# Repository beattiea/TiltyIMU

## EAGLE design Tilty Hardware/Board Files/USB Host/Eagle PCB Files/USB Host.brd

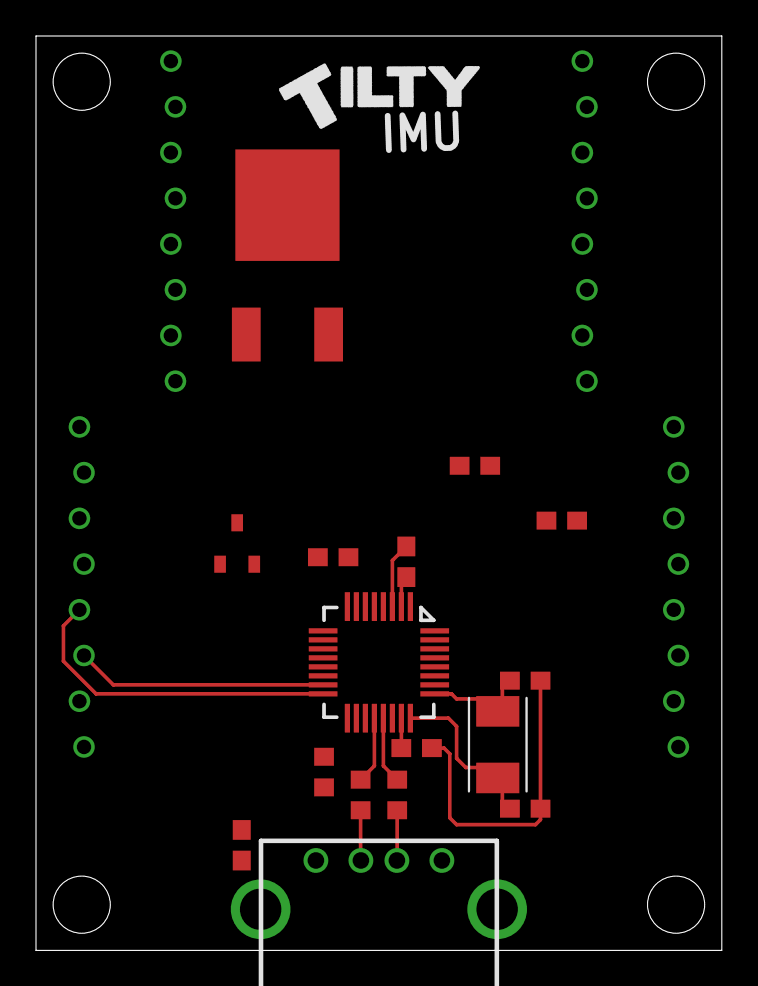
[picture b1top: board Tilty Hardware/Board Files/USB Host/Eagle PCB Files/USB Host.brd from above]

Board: 2 copper layers, 38.1 x 50.8 mm, 20 parts (0 on the bottom side), 16 nets.

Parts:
C1, C2, C7: 0.1uF; C0603
C3, C4: 22pF; C0603
C5, C8: 4.7uF; C0603
C6: 1uF; C0603
JP1, JP2, JP3, JP4: 8-PIN_HEADER; 8-PIN_RECEPTACLE_LOCK_NO-SS
R1, R2: 33; R0603
R3: 4.7K; R0603
U1: MAX3421E; TQFP32_8MIL
U2: AP7313SOT23R; SOT23
U3: LM2931; TO263
U$1: USB_SOCKETTYPE-A; USB_SOCKET
X1: CRYSTAL-TXC-7A

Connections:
+3V3: C1.1, C2.1, C6.1, JP1.P$1, R3.2, U1.2, U1.23, U2.P$2
+5V: C5.1, C8.1, JP4.P$1, U2.P$3, U3.P$3, U$1.P$1
GND: C1.2, C2.2, C3.1, C4.1, C5.2, JP2.P$8, JP3.P$8, JP4.P$2, U1.3, U1.19, U$1.P$4, U$1.P$5, U$1.P$6
INT: R3.1, U1.18
MISO: JP2.P$6, U1.15
MOSI: JP2.P$5, U1.16
unnamed: R2.2, U1.20
unnamed: R1.2, U1.21
unnamed: R2.1, U$1.P$2
unnamed: R1.1, U$1.P$3
unnamed: C4.2, U1.24, X1.P$1
unnamed: C3.2, U1.25, X1.P$2
unnamed: C6.2, U2.P$1
unnamed: C7.2, C8.2, U3.P$1
SCK: JP3.P$5, U1.13
VCC: C7.1, JP2.P$7, U3.P$2

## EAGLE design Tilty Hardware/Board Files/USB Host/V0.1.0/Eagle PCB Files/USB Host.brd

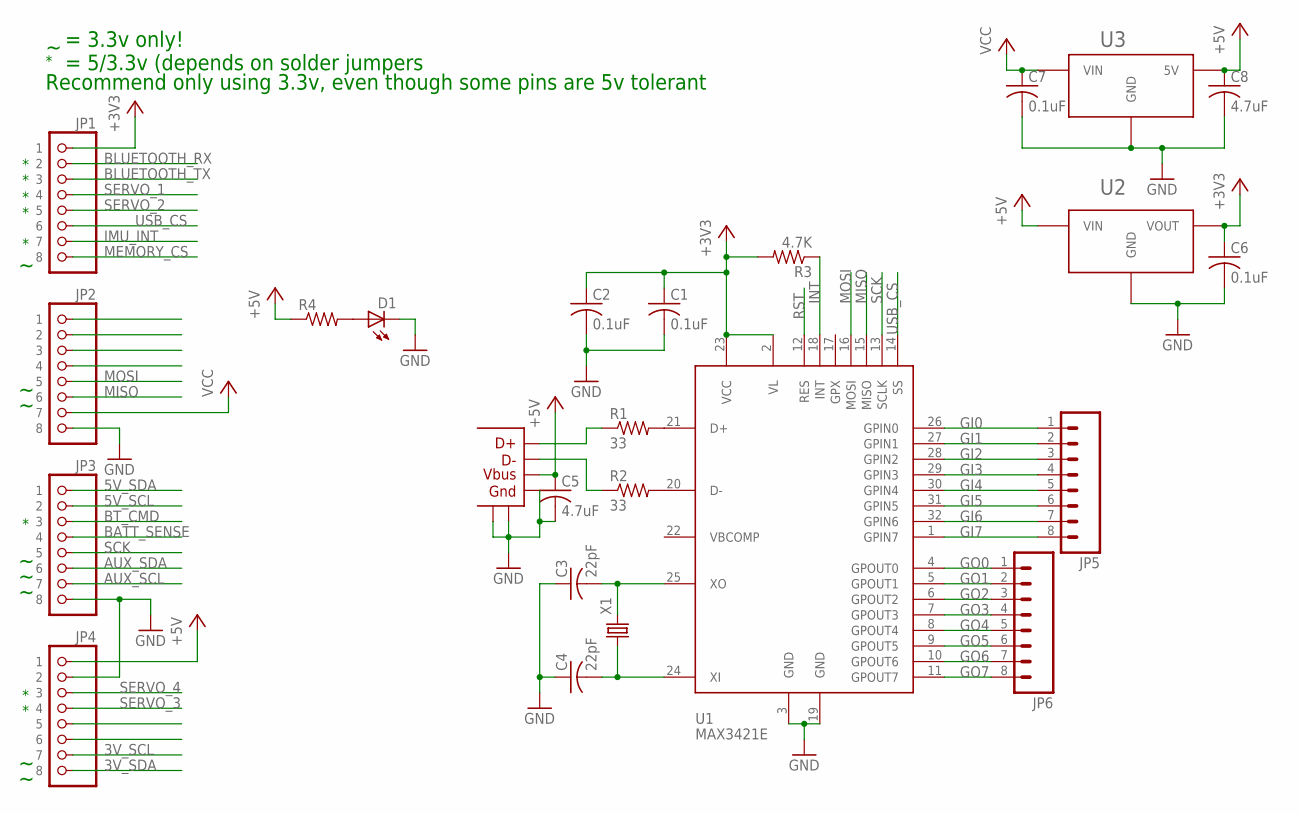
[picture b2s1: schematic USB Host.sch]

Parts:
C1, C2, C6, C7: 0.1uF; C0603
C3, C4: 22pF; C0603
C5, C8: 4.7uF; C0603
D1: LED-GREENLED-0805_NO_SILK; LED-0805
JP1, JP2, JP3, JP4: 8-PIN_HEADER; 8-PIN_RECEPTACLE_LOCK_NO-SS
JP5, JP6: M081X08; 1X08
R1, R2: 33; R0603
R3: 4.7K; R0603
R4: R-US_R0603; R0603
U1: MAX3421E; TQFP32_8MIL
U2: AP7313SOT23R; SOT23
U3: LM2931; TO263
U$1: USB_SOCKETTYPE-A; USB_SOCKET; PART# USB-A1HSW6
X1: CRYSTALTXC-7A; CRYSTAL-TXC-7A; PART# 7A-12.000MAAE-T

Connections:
3V_SCL: JP4.P$7 (7)
3V_SDA: JP4.P$8 (8)
5V_SCL: JP3.P$2 (2)
5V_SDA: JP3.P$1 (1)
+3V3: C1.1, C2.1, C6.1, JP1.P$1 (1), R3.2, U1.2 (VL), U1.23 (VCC), U2.P$2 (VOUT)
+5V: C5.1, C8.1, JP4.P$1 (1), R4.1, U2.P$3 (VIN), U3.P$3 (5V), U$1.P$1 (VBUS)
AUX_SCL: JP3.P$7 (7)
AUX_SDA: JP3.P$6 (6)
BATT_SENSE: JP3.P$4 (4)
BLUETOOTH_RX: JP1.P$2 (2)
BLUETOOTH_TX: JP1.P$3 (3)
BT_CMD: JP3.P$3 (3)
GI0: JP5.1, U1.26 (GPIN0)
GI1: JP5.2, U1.27 (GPIN1)
GI2: JP5.3, U1.28 (GPIN2)
GI3: JP5.4, U1.29 (GPIN3)
GI4: JP5.5, U1.30 (GPIN4)
GI5: JP5.6, U1.31 (GPIN5)
GI6: JP5.7, U1.32 (GPIN6)
GI7: JP5.8, U1.1 (GPIN7)
GND: C1.2, C2.2, C3.1, C4.1, C5.2, C6.2, C7.2, C8.2, D1.2 (C), JP2.P$8 (8), JP3.P$8 (8), JP4.P$2 (2), U1.3 (GND), U1.19 (GND), U2.P$1 (GND), U3.P$1 (GND), U$1.P$4 (GND), U$1.P$5, U$1.P$6
GO0: JP6.1, U1.4 (GPOUT0)
GO1: JP6.2, U1.5 (GPOUT1)
GO2: JP6.3, U1.6 (GPOUT2)
GO3: JP6.4, U1.7 (GPOUT3)
GO4: JP6.5, U1.8 (GPOUT4)
GO5: JP6.6, U1.9 (GPOUT5)
GO6: JP6.7, U1.10 (GPOUT6)
GO7: JP6.8, U1.11 (GPOUT7)
IMU_INT: JP1.P$7 (7)
INT: R3.1, U1.18 (INT)
MEMORY_CS: JP1.P$8 (8)
MISO: JP2.P$6 (6), U1.15 (MISO)
MOSI: JP2.P$5 (5), U1.16 (MOSI)
unnamed: R2.2, U1.20 (D-)
unnamed: R1.2, U1.21 (D+)
unnamed: R2.1, U$1.P$2 (D-)
unnamed: R1.1, U$1.P$3 (D+)
unnamed: D1.1 (A), R4.2
unnamed: C4.2, U1.24 (XI), X1.P$1 (1)
unnamed: C3.2, U1.25 (XO), X1.P$2 (2)
RST: U1.12 (RES)
SCK: JP3.P$5 (5), U1.13 (SCLK)
SERVO_1: JP1.P$4 (4)
SERVO_2: JP1.P$5 (5)
SERVO_3: JP4.P$4 (4)
SERVO_4: JP4.P$3 (3)
USB_CS: JP1.P$6 (6), U1.14 (SS)
VCC: C7.1, JP2.P$7 (7), U3.P$2 (VIN)

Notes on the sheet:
= 3.3v only!
= 5/3.3v (depends on solder jumpers
Recommend only using 3.3v, even though some pins are 5v tolerant

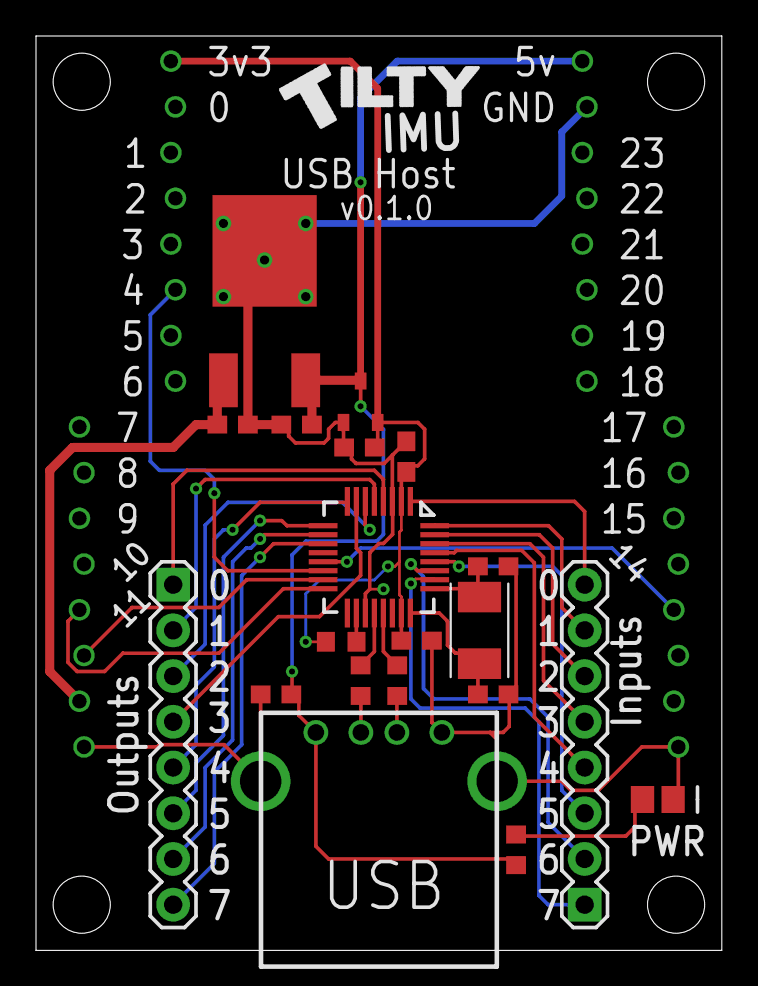
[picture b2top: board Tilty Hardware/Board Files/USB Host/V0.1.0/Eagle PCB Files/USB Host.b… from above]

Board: 2 copper layers, 38.1 x 50.8 mm, 24 parts (0 on the bottom side), 32 nets.

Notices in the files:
parts and their libraries:
SparkFun-FreqCtrl: Licensing: CC v3.0 Share-Alike You are welcome to use this library for commercial purposes.
